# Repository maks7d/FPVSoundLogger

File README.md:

# FPVSoundLogger
A DIY RP2040-Zero based onboard audio recorder for FPV drones. It uses a MEMS mic and SD card module to capture sound, automatically triggered by Betaflight arming via PinioBox. Recordings match DJI goggles video length for seamless editing. Includes hardware design, MicroPython code, and examples.

###### Enjoy this project or find it useful? Feel free to buy me a coffee ☕ to support its development. 

## Project Background

I first started experimenting with the excellent and promising [OpenIPC](https://github.com/openipc) project, driven by my love for tinkering, hacking, and coding. The idea of building an open FPV video system was incredibly appealing.
But after many tests, the freeze issues and limited range eventually convinced me to switch to DJI for reliable everyday flying.
(But I promise — I’ll come back to OpenIPC!)

The DJI O4 Air Unit provides fantastic onboard video recordings.
But (because there's always a “but”), it still doesn’t record audio. And audio truly adds something special — whether for aggressive FPV flying or even some cinematic flights.

So I wanted a solution that would be simple/lightweight/inexpensive and capable of recording high‑quality audio and perfectly* synchronized with DJI recordings.
This project is the result of that idea.

##### Démo

## Features
- Autonomous module
- Work with [Betaflight](https://github.com/betaflight/betaflight)/[INAV](https://github.com/iNavFlight/inav) 
- Enable/disable recording
- Auto record using arm/disarm trigger
- Audio/video share the same duration*

## Prerequisites

- A flight controller running **[Betaflight](https://github.com/betaflight/betaflight)**/**[INAV](https://github.com/iNavFlight/inav)** with at least two available Pinio outputs
- A transmitter (TX) capable of assigning **AUX channels** (EdgeTX, OpenTX, etc.)
- A stable **3.3V** output on the flight controller and a **common ground**
- A free **switch** or similar to toggle recording modes
- Basic soldering tools for connecting power, ground, and signal wires and plenty of flux — <u>***flux is life***</u>

## How It Works

- Power up the drone — In **Disable** mode module's LED **Red** blinking 🔴
- Use one of your TX switches to **Enable** recording mode — the LED now blinks **Green** 🟢
- **Arm**: the module immediately starts **writing audio data** to the SD card, and the LED now blinks **Blue** 🔵
- **Once disarmed** — whether after a normal end of flight or a dramatic crash — the module **stops recording** and finalizes the audio file with the proper header
- Remove the SD card and retrieve the **WAV file** that matches the exact flight duration
- Import the audio into your favorite video editor and drop it on the timeline — it syncs effortlessly with the DJI footage !
> **⚠️ Fine-tuning tip:** Due to DJI's camera initialization delay after arming, 
> you may need to offset the audio track by **0.5-2 seconds** in your editor. 

**Format:** `rec_XXXX_MM-SS.wav`
- 🔵 **Index (XXXX)**: Auto-incremented counter (0001, 0002, 0003...)
- 🟡 **Duration (MM-SS)**: Recording length in minutes and seconds

## Architecture / Hardware Overview

### Components

|  | INMP441 | RP2040-Zero | SD Card SPI Module |
| - | :-------: | :-----------: | :-------------: |
| | |  |  |
| Description | The INMP441 is a compact digital MEMS microphone that outputs audio through an I²S interface.It delivers low‑noise, high‑quality audio capture with a built‑in amplifier and ADC | The Raspberry Pi Pico uses the RP2040 dual‑core ARM Cortex‑M0+ microcontroller running at up to 133 MHz with 264 KB RAM and 2 MB flash.It offers rich connectivity like I²C, SPI, UART, PWM, ADC, and powerful PIO blocks for custom protocols.Compact, low‑cost, and easy to program in **MicroPython** or C/C++.| Micro SD TF Card Memory Shield Module provides an easy way to add microSD storage to microcontrollers.It uses an onboard card socket and level shifting for safe 3.3 V–5 V operation.Ideal for large dataqqsets via SPI. |
| Size | 12x14mm | 18x24.5mm | 18x21mm |
| Weight | 0.36gr | 1.66gr | 1.46gr |
| AliExpress | [INMP441](https://www.aliexpress.com/item/1005007889064664.html?spm=a2g0o.order_list.order_list_main.142.32325e5blt8IZ0) | [RP20240-Zero](https://www.aliexpress.com/item/1005007650325892.html?spm=a2g0o.order_list.order_list_main.147.32325e5blt8IZ0) | [SD TF Module](https://www.aliexpress.com/item/1005005591145849.html?spm=a2g0o.order_list.order_list_main.152.32325e5blt8IZ0) |

### Wiring

### Alternatives
An alternative is to use the FC’s 5 V rail to power the Pi Pico. The SD Card SPI module can convert data signals to 3.3 V levels, allowing it to use the Pi Pico’s 5 V rail. However, according to the [INMP441](resources/datasheet/INMP441.pdf) datasheet, the maximum supply voltage must not exceed 3.63 V, so **you must power it from the Pi Pico’s 3.3 V rail**.

## Build 

In the interest of keeping things lightweight and considering the very low current required for the system to operate, 28‑AWG silicone cable is more than sufficient, and you shouldn’t add more than 1 g to the whole setup.I cut and glued a small foam circle — the kind you find at the bottom of FC/ESC boxes, as dense as possible — to make a windscreen/pop filter.

Be careful not to get any glue into the microphone’s input opening.To keep everything in place, I used a ridiculously heavy piece of heat‑shrink tubing to “thermal‑zipper” the whole thing, along with a bit of hot glue (B7000 is obviously the best option, though hard to find) to secure the small 4‑pin JST connector against the assembly.

In my rough version installed in my Jeno 5", the module weighs about 10 g, but it’s definitely possible to do much better.

A voltage spike can cause parasitic artifacts in the recording. I haven’t tested this yet, but as mentioned in the [INMP441](resources/datasheet/INMP441.pdf) datasheet it is recommended to use a small 0.1 µF ceramic capacitor between VDD and GND.

##### Examples

## Installation & Configuration

### Pi Pico: Flashing MicroPython on an RP2040 with Thonny

##### 1. Install Thonny
- Download and install [Thonny](https://thonny.org/) from the official website.  
- Open [Thonny](https://thonny.org/).

##### 2. Put the RP2040 board into bootloader mode
- Plug in the board **while holding the BOOTSEL button**.  
- Release the button once connected: the board should appear as a USB drive named **RPI-RP2**.

##### 3. Install MicroPython from [Thonny](https://thonny.org/)
- In Thonny, go to:  
  **Tools → Options… → Interpreter**  
- Select:  
  **MicroPython (Raspberry Pi Pico / RP2040)**  
- Click **Install or update MicroPython**.  
- Select your **RPI-RP2** device.  
- Start the installation.

##### 4. Automatic restart
The board will reboot with MicroPython installed.  
[Thonny](https://thonny.org/) should now display a `>>>` prompt.

##### 5. Quick test
Type:

```python
print(f"WE ARE {'fpv'.upper()}")
```

##### 6. Project files to upload
```
├── main.py                    # Main application (auto-runs on boot)
   └── lib/
       ├── sdcard.py              # SD card driver
       └── fpv_sound_logger.py    # Core logger class
```

- In Thonny, go to **View > Files**
- In your computer's file panel (left side), navigate to your project folder
- Select the `lib` folder
- Right-click → **"Upload to /"**
- Then select `main.py`
- Right-click → **"Upload to /"**
- Thonny will upload the entire structure automatically

> **Note:** This method preserves the folder structure. The `lib` folder and its contents will be uploaded correctly.

### TX && Betaflight configuration

All you need to know about Betaflight's Pinio && PinioBox can be found [here](https://www.betaflight.com/docs/wiki/guides/current/Pinio-and-PinioBox), I also got some excellent advice from Betaflight’s [official discord](https://discord.betaflight.com/)

- You'll need to configure AUX channel on your TX to Enable/Disable recording

    > I configured it to use the center position of an three-position switch mapped to AUX6 on my Radiomaster Pocket running on EdgeTX.

- Provide a **common ground** from the flight controller to the module, along with a clean **3.3V** or [5V supply](#Alternatives)

    > On my JHEMCU GF20F722, I used the 3.3V rail that was originally intended for a DSM receiver.

- Configure your flight controller’s Pinio outputs using CLI to deliver the required logic levels:

    - One Pinio controls record enable/disable

    - The second Pinio follows the arm/disarm sequence to automatically start and stop recording.

    > [...]
    > 
    > resource pinio 1 B10          # remap RX3 pad
    > 
    > resource pinio 2 B11          # remap TX3 pad
    > 
    > set pinio_config = 1,129,1,1  # High level for _pinio 1_ and inverted for _pinio 2_
    > 
    > set pinio_box = 40,0,255,255  # ID 40 mean BOXUSER1 and ID 0 Arm/Disarms

- Configure a new mode for USER1

### For testing purposes

Even if the 3.3 V or 5 V rail used to power the recorder is active while [Betaflight](https://github.com/betaflight/betaflight) is connected via USB, you still won’t be able to start the recording. The [Betaflight](https://github.com/betaflight/betaflight) safety flags will prevent the drone from arming.

Because of this, even with the ***MOTOR_STOP*** option enabled in the Motors tab, the brushless motors may still start spinning. As a result, you will always have motor or propeller noise in your recordings — never any silence. And if you need to speak into the microphone, **be careful**… or make sure to shout loud enough! ^^

###### TODO
A lot ...!?

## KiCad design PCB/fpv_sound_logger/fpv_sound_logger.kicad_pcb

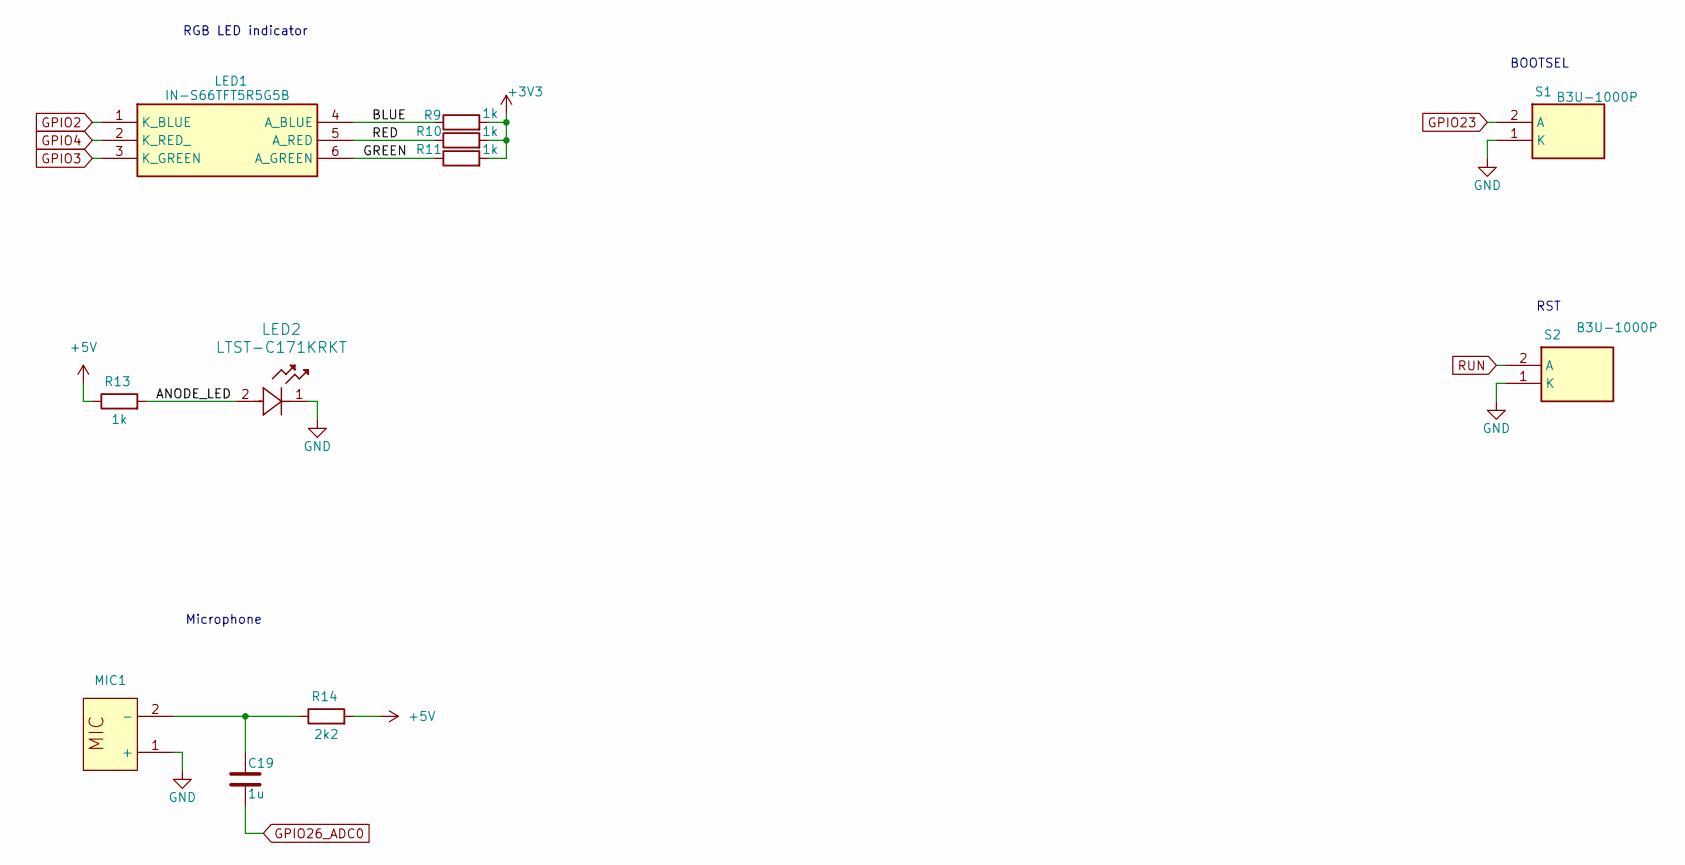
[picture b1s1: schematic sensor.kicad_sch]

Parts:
C19: 1u; C_0603_1608Metric; Manufacturer_Part_Number CL10B105KA8NNNC
LED1: IN-S66TFT5R5G5B; INS66TFT5R5G5B; Mouser Part Number 743-IN-S66TFT5R5G5B
LED2: LTST-C171KRKT; LED_LTST-C171_LTO-M; Manufacturer_Part_Number LTST-C171KRKT
MIC1: MIC-TH_BD6.0-P1.90-D0.4-L-FD_GMI6050P-2CXXDB; Manufacturer Part GMI6050P-36db; LCSC Part Name 全指向φ6.0*5.0mm 1.5V-10V 灵敏度-36db 低阻抗 针脚
R9, R10, R11, R13: 1k; R_0603_1608Metric; Manufacturer_Part_Number ERJ3EKF1001V
R14: 2k2; R_0603_1608Metric; Manufacturer_Part_Number ERJ3EKF1001V
S1, S2: B3U-1000P; Mouser Part Number 653-B3U-1000P

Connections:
+3V3: R9.2, R10.2, R11.2; also elsewhere on the board
+5V: R13.1, R14.2; also elsewhere on the board
/sensor/ANODE_LED: LED2.2, R13.2
/sensor/BLUE: LED1.4 (A_BLUE), R9.1
/sensor/GREEN: LED1.6 (A_GREEN), R11.1
/sensor/RED: LED1.5 (A_RED), R10.1
GND: LED2.1, MIC1.1 (+), S1.1 (K), S2.1 (K); also elsewhere on the board
GPIO2: LED1.1 (K_BLUE); also elsewhere on the board
GPIO3: LED1.3 (K_GREEN); also elsewhere on the board
GPIO4: LED1.2 (K_RED_); also elsewhere on the board
GPIO23: S1.2 (A); also elsewhere on the board
GPIO26_ADC0: C19.2; also elsewhere on the board
unnamed: C19.1, MIC1.2 (-), R14.1
RUN: S2.2 (A); also elsewhere on the board

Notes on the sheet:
RST
RGB LED indicator
BOOTSEL
Microphone

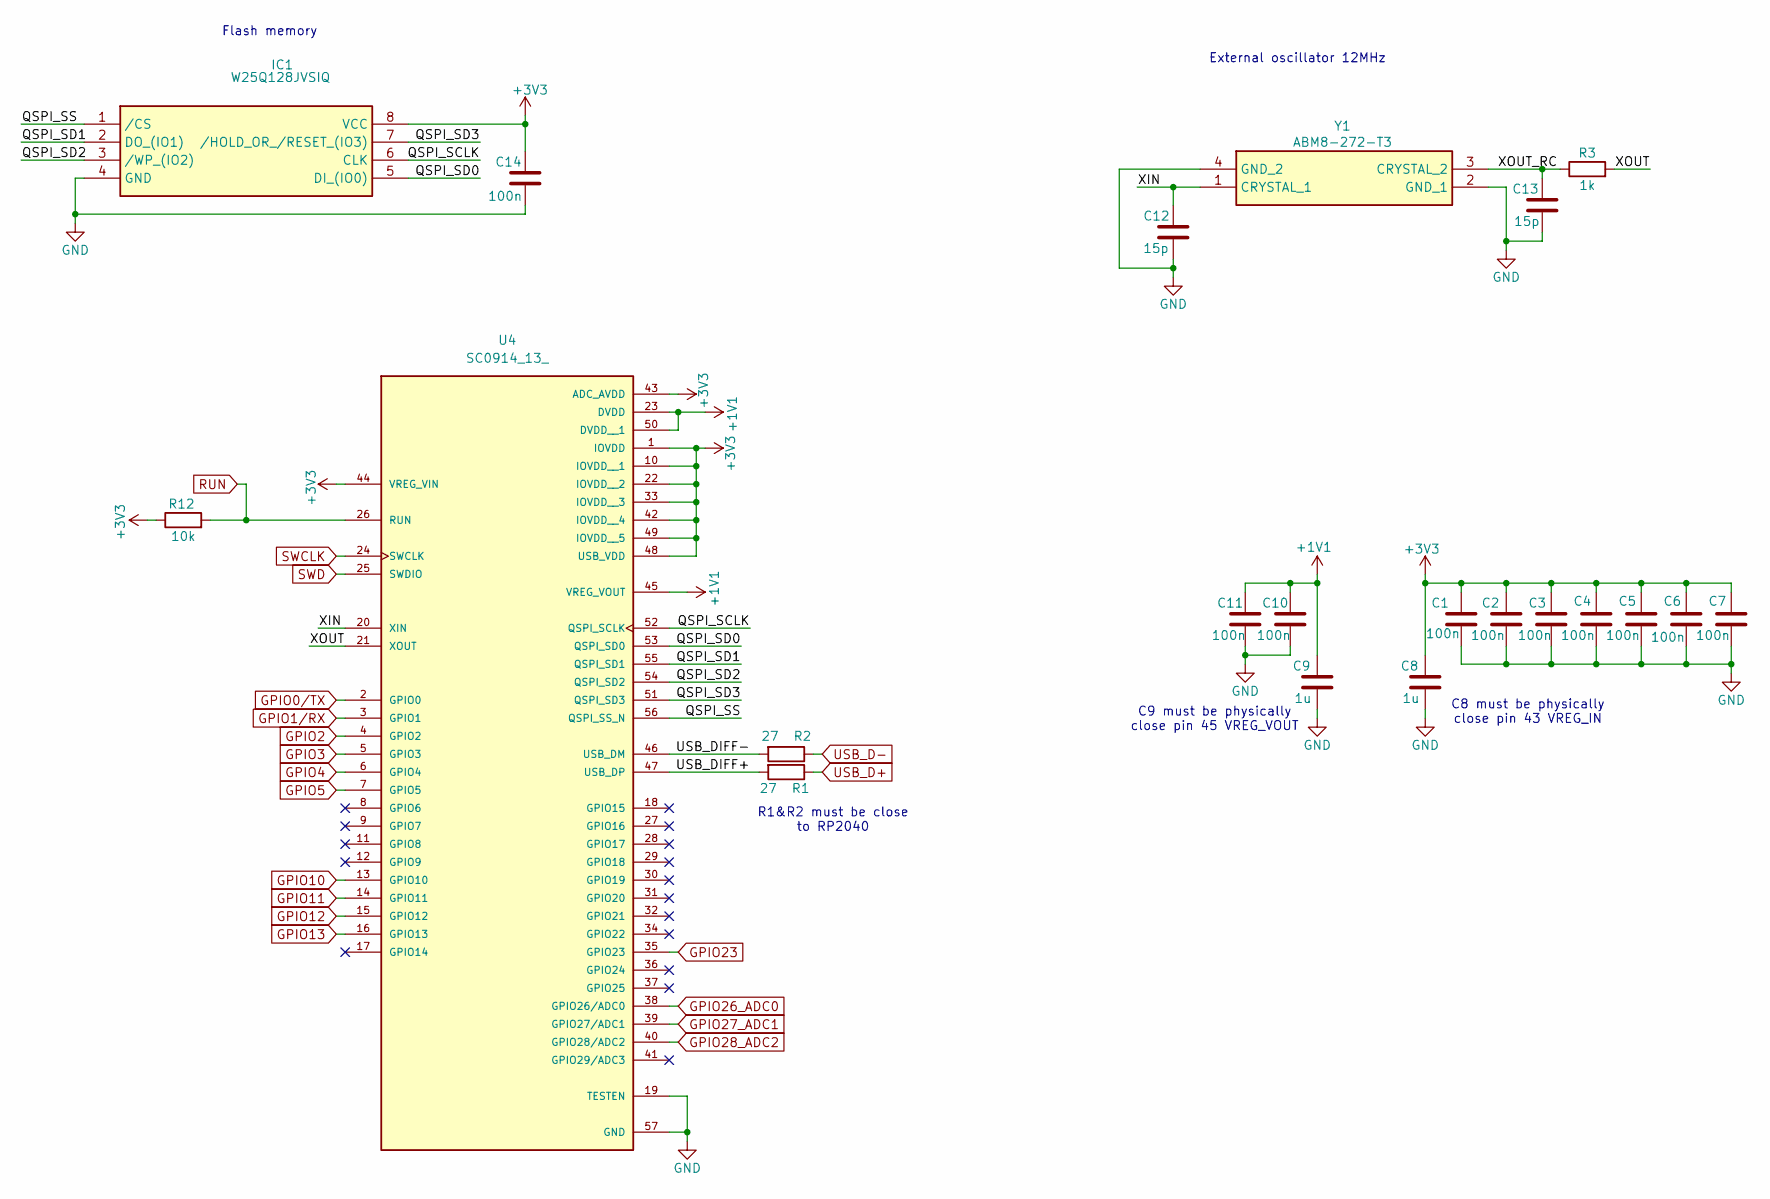
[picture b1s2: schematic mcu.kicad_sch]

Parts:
C1, C2, C3, C4, C5, C6, C7, C10, C11, C14: 100n; C_0603_1608Metric; Manufacturer_Part_Number CL10B104KB8NNNC
C8, C9: 1u; C_0603_1608Metric; Manufacturer_Part_Number CL10B105KA8NNNC
C12, C13: 15p; C_0603_1608Metric; Manufacturer_Part_Number CL10C150JB8NNNC
IC1: W25Q128JVSIQ; SOIC127P790X216-8N; Mouser Part Number 454-W25Q128JVSIQ
R1, R2: 27; R_0603_1608Metric; Manufacturer_Part_Number ERJ3EKF27R0V
R3: 1k; R_0603_1608Metric; Manufacturer_Part_Number ERJ3EKF1001V
R12: 10k; R_0603_1608Metric; Manufacturer_Part_Number ERJUP3F1002V
U4: SC0914_13_; QFN40P700X700X90-57N; PARTREV 2.2
Y1: ABM8-272-T3; ABM8272T3; Mouser Part Number 815-ABM8-272-T3

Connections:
+1V1: C9.1, C10.1, C11.1, U4.23 (DVDD), U4.45 (VREG_VOUT), U4.50 (DVDD__1)
+3V3: C1.1, C2.1, C3.1, C4.1, C5.1, C6.1, C7.1, C8.1, C14.1, IC1.8 (VCC), R12.1, U4.1 (IOVDD), U4.10 (IOVDD__1), U4.22 (IOVDD__2), U4.33 (IOVDD__3), U4.42 (IOVDD__4), U4.43 (ADC_AVDD), U4.44 (VREG_VIN), U4.48 (USB_VDD), U4.49 (IOVDD__5); also elsewhere on the board
/MCU/QSPI_SCLK: IC1.6 (CLK), U4.52 (QSPI_SCLK)
/MCU/QSPI_SD0: IC1.5 (DI_(IO0)), U4.53 (QSPI_SD0)
/MCU/QSPI_SD1: IC1.2 (DO_(IO1)), U4.55 (QSPI_SD1)
/MCU/QSPI_SD2: IC1.3 (/WP_(IO2)), U4.54 (QSPI_SD2)
/MCU/QSPI_SD3: IC1.7 (/HOLD_OR_/RESET_(IO3)), U4.51 (QSPI_SD3)
/MCU/QSPI_SS: IC1.1 (/CS), U4.56 (QSPI_SS_N)
/MCU/USB_DIFF+: R1.2, U4.47 (USB_DP)
/MCU/USB_DIFF-: R2.2, U4.46 (USB_DM)
/MCU/XIN: C12.1, U4.20 (XIN), Y1.1 (CRYSTAL_1)
/MCU/XOUT: R3.2, U4.21 (XOUT)
/MCU/XOUT_RC: C13.1, R3.1, Y1.3 (CRYSTAL_2)
GND: C1.2, C2.2, C3.2, C4.2, C5.2, C6.2, C7.2, C8.2, C9.2, C10.2, C11.2, C12.2, C13.2, C14.2, IC1.4 (GND), U4.19 (TESTEN), U4.57 (GND), Y1.2 (GND_1), Y1.4 (GND_2); also elsewhere on the board
GPIO0/TX: U4.2 (GPIO0); also elsewhere on the board
GPIO1/RX: U4.3 (GPIO1); also elsewhere on the board
GPIO2: U4.4 (GPIO2); also elsewhere on the board
GPIO3: U4.5 (GPIO3); also elsewhere on the board
GPIO4: U4.6 (GPIO4); also elsewhere on the board
GPIO5: U4.7 (GPIO5)
GPIO10: U4.13 (GPIO10); also elsewhere on the board
GPIO11: U4.14 (GPIO11); also elsewhere on the board
GPIO12: U4.15 (GPIO12); also elsewhere on the board
GPIO13: U4.16 (GPIO13); also elsewhere on the board
GPIO23: U4.35 (GPIO23); also elsewhere on the board
GPIO26_ADC0: U4.38 (GPIO26/ADC0); also elsewhere on the board
GPIO27_ADC1: U4.39 (GPIO27/ADC1)
GPIO28_ADC2: U4.40 (GPIO28/ADC2)
RUN: R12.2, U4.26 (RUN); also elsewhere on the board
SWCLK: U4.24 (SWCLK); also elsewhere on the board
SWD: U4.25 (SWDIO); also elsewhere on the board
USB_D+: R1.1; also elsewhere on the board
USB_D-: R2.1; also elsewhere on the board

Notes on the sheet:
External oscillator 12MHz
C9 must be physically close pin 45 VREG_VOUT
R1&R2 must be close to RP2040
C8 must be physically close pin 43 VREG_IN
Flash memory

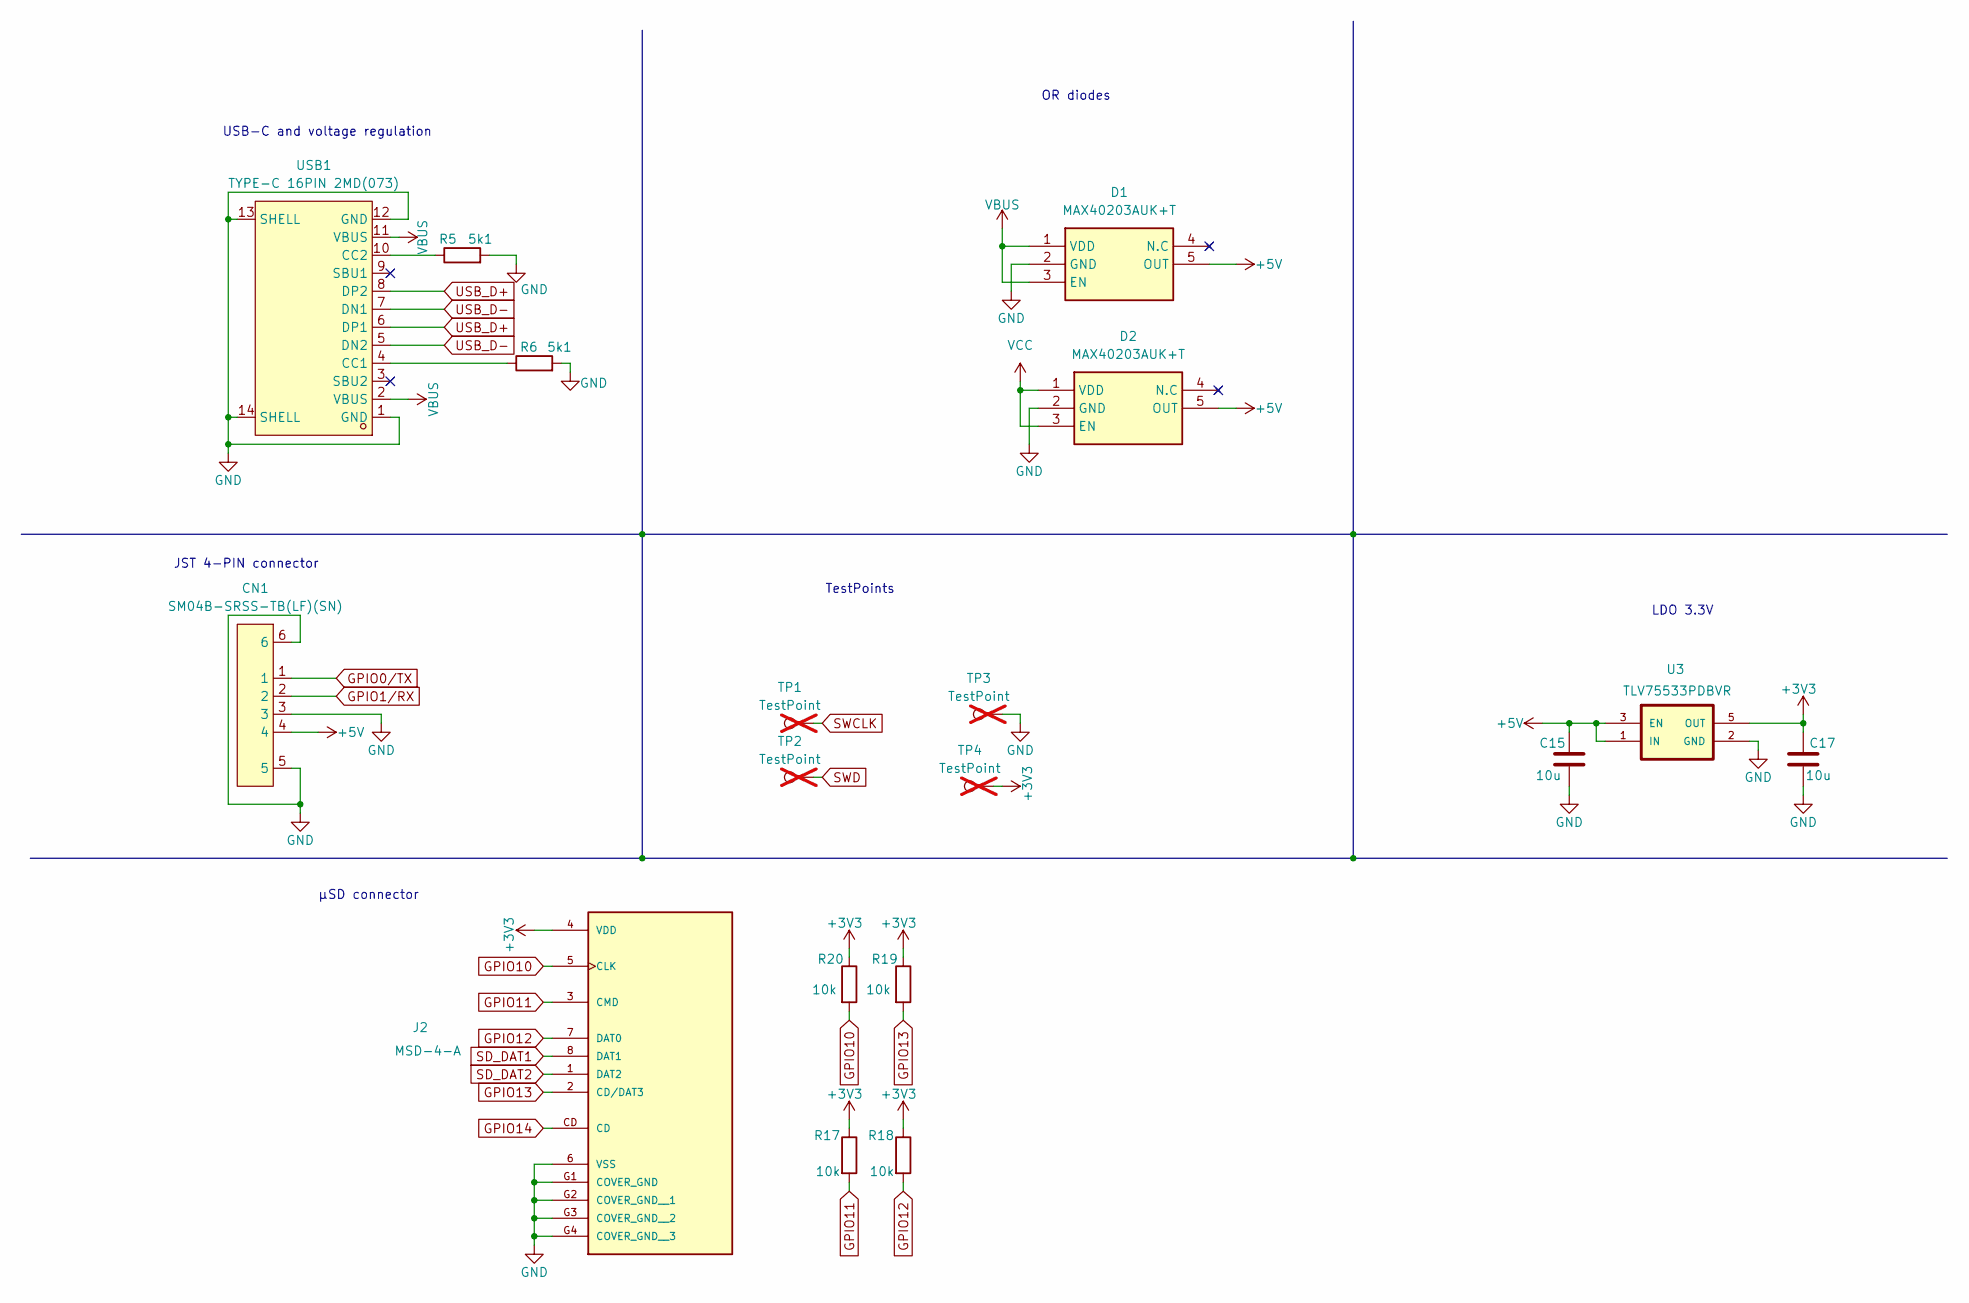
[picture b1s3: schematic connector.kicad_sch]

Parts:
C15, C17: 10u; C_0603_1608Metric; Manufacturer_Part_Number CL10A106MQ8NNNC
CN1: SM04B-SRSS-TB(LF)(SN); CONN-SMD_4P-P1.00_SM04B-SRSS-TB-LF-SN; Manufacturer Part SM04B-SRSS-TB(LF)(SN); LCSC Part Name 1x4P 间距:1mm 卧贴 系列:SH
D1, D2: MAX40203AUK+T; SOT95P280X145-5M; Mouser Part Number 700-MAX40203AUK+T
J2: MSD-4-A; CUI_MSD-4-A; PARTREV 1.0
R5, R6: 5k1; R_0603_1608Metric; Manufacturer_Part_Number ERA3AEB512V
R17, R18, R19, R20: 10k; R_0603_1608Metric; Manufacturer_Part_Number ERJUP3F1002V
TP1, TP2, TP3, TP4: TestPoint; TestPoint_Pad_D1.0mm; not fitted
U3: TLV75533PDBVR; SOT95P280X145-5N; Manufacturer_Part_Number TLV75533PDBVR
USB1: TYPE-C 16PIN 2MD(073); USB-C-SMD_TYPE-C-6PIN-2MD-073; Manufacturer Part TYPE-C 16PIN 2MD(073); LCSC Part Name Type-C 母 卧贴

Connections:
+3V3: C17.1, J2.4 (VDD), R17.1, R18.1, R19.1, R20.1, TP4.1 (1_1), U3.5 (OUT); also elsewhere on the board
+5V: C15.1, CN1.4, D1.5 (OUT), D2.5 (OUT), U3.1 (IN), U3.3 (EN); also elsewhere on the board
GND: C15.2, C17.2, CN1.3, CN1.5, CN1.6, D1.2 (GND), D2.2 (GND), J2.6 (VSS), J2.G1 (COVER_GND), J2.G2 (COVER_GND__1), J2.G3 (COVER_GND__2), J2.G4 (COVER_GND__3), R5.2, R6.2, TP3.1 (1_1), U3.2 (GND), USB1.1 (GND), USB1.12 (GND), USB1.13 (SHELL), USB1.14 (SHELL); also elsewhere on the board
GPIO0/TX: CN1.1; also elsewhere on the board
GPIO1/RX: CN1.2; also elsewhere on the board
GPIO10: J2.5 (CLK), R20.2; also elsewhere on the board
GPIO11: J2.3 (CMD), R17.2; also elsewhere on the board
GPIO12: J2.7 (DAT0), R18.2; also elsewhere on the board
GPIO13: J2.2 (CD/DAT3), R19.2; also elsewhere on the board
GPIO14: J2.CD
unnamed: R6.1, USB1.4 (CC1)
unnamed: R5.1, USB1.10 (CC2)
SD_DAT1: J2.8 (DAT1)
SD_DAT2: J2.1 (DAT2)
SWCLK: TP1.1 (1_1); also elsewhere on the board
SWD: TP2.1 (1_1); also elsewhere on the board
USB_D+: USB1.6 (DP1), USB1.8 (DP2); also elsewhere on the board
USB_D-: USB1.5 (DN2), USB1.7 (DN1); also elsewhere on the board
VBUS: D1.1 (VDD), D1.3 (EN), USB1.2 (VBUS), USB1.11 (VBUS)
VCC: D2.1 (VDD), D2.3 (EN)

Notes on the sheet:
USB-C and voltage regulation
OR diodes
TestPoints
JST 4-PIN connector
µSD connector
LDO 3.3V

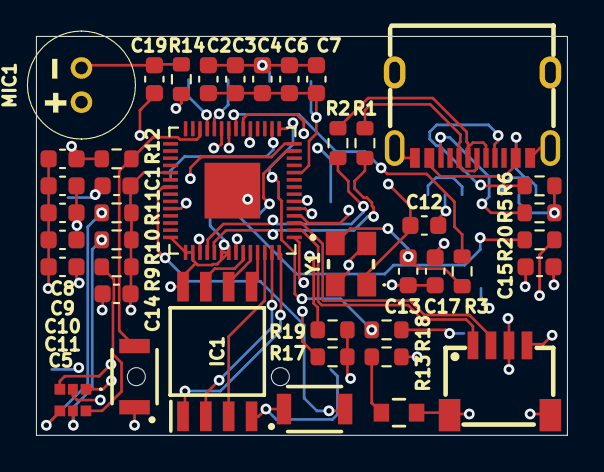
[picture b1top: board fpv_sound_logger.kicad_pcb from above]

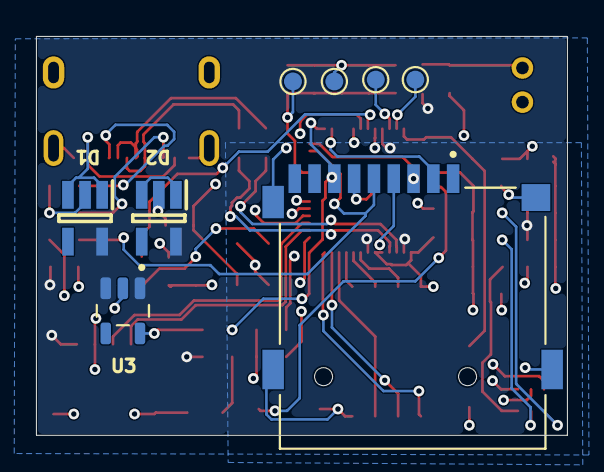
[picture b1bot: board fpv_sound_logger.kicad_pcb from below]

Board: 4 copper layers, 29.5 x 22.2 mm, 50 parts (8 on the bottom side), 40 nets.

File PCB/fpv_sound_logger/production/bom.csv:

Designator,Footprint,Quantity,Value,LCSC Part #
"C1, C10, C11, C14, C2, C3, C4, C5, C6, C7",0603,10,100n,
"C12, C13",0603,2,15p,
"C15, C17",0603,2,10u,
"C19, C8, C9",0603,3,1u,
CN1,CONN-SMD_4P-P1.00_SM04B-SRSS-TB-LF-SN,1,SM04B-SRSS-TB(LF)(SN),
"D1, D2",SOT95P280X145-5M,2,MAX40203AUK+T,
IC1,SOIC127P790X216-8N,1,W25Q128JVSIQ,
J2,CUI_MSD-4-A,1,MSD-4-A,
LED1,INS66TFT5R5G5B,1,IN-S66TFT5R5G5B,
LED2,LED_LTST-C171_LTO-M,1,LTST-C171KRKT,
MIC1,MIC-TH_BD6.0-P1.90-D0.4-L-FD_GMI6050P-2CXXDB,1,~,
"R1, R2",0603,2,27,
"R10, R11, R13, R3, R9",0603,5,1k,
"R12, R17, R18, R19, R20",0603,5,10k,
R14,0603,1,2k2,
"R5, R6",0603,2,5k1,
"S1, S2",B3U-1000P,2,B3U-1000P,
U3,SOT95P280X145-5N,1,TLV75533PDBVR,
U4,QFN40P700X700X90-57N,1,SC0914_13_,
USB1,USB-C-SMD_TYPE-C-6PIN-2MD-073,1,TYPE-C 16PIN 2MD(073),
Y1,ABM8272T3,1,ABM8-272-T3,

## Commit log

2025-12-16 v1.0.0
2025-12-16 fix typo
2025-12-16 add notes in ## How It Works
2025-12-16 typo
2025-12-16 led indicator
2025-12-17 add yt link
2025-12-17 reorder
2025-12-17 Add first iteration of PCB design on kicad
2025-12-17 PCB: add every components, now designing according to datasheets
2025-12-17 PCB: add JST connector, shottky diode, and few debugging
2025-12-18 PCB: finished schematic, started placing components, not decided yet for board dimensions
2025-12-18 PCB: started routing
2025-12-18 PCB: finised routing - Changed clearance from 0.2 to 0.15 in the net class settings. - Increased track width from 0.3 to 0.4 for improved signal integrity. - Added a new net class for POWER with patt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
2025-12-18 PCB: finishes on board design - DRC check - Placed text - add 3d files for 3d viewer
2026-04-24 Refactor code structure and remove redundant sections for improved readability and maintainability
2026-04-25 place new components and started routing for v2
2026-05-15 Update component footprints and add manufacturer details in sensor schematic
    - Changed resistor footprint from R_0805 to R_0603 for multiple components.
    - Updated manufacturer part numbers, manufacturers, suppliers, and supplier parts for various components.
    - Added manufacturer and supplier information for OMRON components.
    - Removed outdated datasheet link and replaced with relevant part numbers for clarity.
2026-05-16 Refactor code structure for improved readability and maintainability
2026-05-17 Update PCB design and netlist for fpv_sound_logger
    - Added new segments and vias for microphone and GPIO connections in the PCB layout.
    - Removed redundant segments related to GPIO26_ADC0 and MIC1 in the PCB layout.
    - Updated active layer in the project file to improve visibility.
    - Modified visible layers in the project file for better layer management.
    - Adjusted netlist to include new connections for MIC1 and GPIO26_ADC0.
    - Changed manufacturer and supplier part numbers for components in the schematic.
